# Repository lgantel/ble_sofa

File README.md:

# BLE Sofa
Control module for CIAR sofa using custom BLE interface.

## Overview

The sofa command box is powered over a 4 pins RJ9 connector. The voltage measured at the command box input is 29V. It is provided by the motor (LM35_05) which gets its power from the PS10 adapter (29V - 2A).

The command box has three cable inputs:
- The RJ9 connector for power supply and motor commands
- The left input (J1) connected to the sensitive button; It corresponds to the Down command.
- The right input (J3) connected to the other sensitive button; It corresponds to the Up command.

## Power Supply and Motor Commands

The RJ9 connector provides 4 wires connection which supplies power from the motor to the control box, and Up and Down commands from the control box to the motor.

## Issue with the current system

Currently the command box is connected to the Up and Down button with electrical wires. The issue comes when moving the sofa up and down, the cables are compressed by the mechanical part and end up being damaged.

## Replacement Solution

A replacement solution has been specified to allow the user to control the sofa using a wireless BLE application. The system would be based on a Raspberry Pi Pico W module which permits to easily control the motor through two electrical relays, and to receive commands from the user via the Bluetooth stack.

# Tools Setup

## Get the SDK and examples

```bash
cd pico
git clone https://github.com/raspberrypi/pico-sdk.git --branch master
cd pico-sdk
git submodule update --init
cd ..
git clone https://github.com/raspberrypi/pico-examples.git --branch master
```

## Install the toolchain

1. Install dependencies:

```bash
sudo apt update
sudo apt install cmake gcc-arm-none-eabi libnewlib-arm-none-eabi build-essential libstdc++-arm-none-eabi-newlib pkg-config libusb-1.0-0-dev
```

2. In the bashrc file, export the path to the SDK:

```bash
#
# RPi Pico SDK
#
export PICO_SDK_PATH=/home/laurent/Projects/lgantel/ble_sofa/pico/pico-sdk
```

3. To complete the installation, install `picotool` which is used to generate the UF2 binaries for the Raspberry Pi Pico:

```bash
git clone https://github.com/raspberrypi/picotool.git
cd picotool
mkdir build && cd build
cmake ..
make
sudo make install
```

# Example Projects

```bash
cd pico/workspace
mkdir build
cd build
```

The following examples can be built:

- [LED Control](doc/example_projects.md#led-control)
- [BLE Control](doc/example_projects.md#ble-control)
- [FreeRTOS App](doc/example_projects.md#freertos-app)
- [Relay Control](doc/example_projects.md#relay-control)

# Firmware loading via OpenOCD

1. Install OpenOCD:

```bash
sudo apt-get install pkg-config libjim-dev
git clone https://github.com/raspberrypi/openocd.git
cd openocd
git submodule update --init --recursive
./bootstrap
./configure --enable-picoprobe --enable-sysfsgpio --enable-bcm2835gpio
make -j8
sudo make install
```

2. Connect a USB cable to the Rasperry Pi Pico

3. Program Flash and verify:

```bash
./openocd_launch.sh
```

# BLE Sofa Application

- [BLE Sofa Application Documentation](doc/ble_sofa_app.md#ble_sofa_app)

# Resources

## Raspberry Pi Pico

* Raspberry Pi Pico power pins information:

https://dronebotworkshop.com/pi-pico/

* A nice development kit PCB example for Raspberry Pi Pico:

https://01001000.xyz/2021-02-13-Raspberry-Pi-Pico-dev-board-Kiwikit/

* C library for LCD OLED:

https://github.com/martinkooij/pi-pico-ss-oled

* Information on the debug probes:

https://www.framboise314.fr/tout-nouveau-la-sonde-de-debogage-raspberry-pi-debug-probe/

* Kicad symbol and footprint models:

https://github.com/bdubs-astro/Raspberry_Pi_Pico_W_Kicad_Files

## Bluetooth Low Energy

* Bluetooth BLE resources:

http://tvaira.free.fr/bts-sn/activites/activite-ble/bluetooth-ble.html#gatt-et-att

https://novelbits.io/bluetooth-gatt-services-characteristics/

https://www.jaredwolff.com/get-started-with-bluetooth-low-energy/

https://punchthrough.com/android-ble-guide/

https://mcuoneclipse.com/2023/03/19/ble-with-wifi-and-freertos-on-raspberry-pi-pico-w/

## Pico W Web Server

* https://github.com/krzmaz/pico-w-webserver-example
* https://github.com/carlk3/FreeRTOS-FAT-CLI-for-RPi-Pico/tree/master/examples/wifi_httpd
* https://www.hackster.io/rajivcodelab/how-to-build-a-rest-api-on-raspberry-pi-pico-w-control-led-91b25b

- Rest API client:

https://stackoverflow.com/questions/72252577/what-is-the-simplest-way-to-make-a-post-request-in-kotlin-for-android-app

```bash
curl -X POST "http://192.168.1.31:80/api/control-led" -d '{"led": 0}' -H 'Content-Type: application/json'
```

## Flash Storage

* Tutorial on how to modify linker script to reserve a flash memory block for persistent storage:

https://community.element14.com/products/raspberry-pi/b/blog/posts/raspberry-pico-c-sdk-reserve-a-flash-memory-block-for-persistent-storage

* Example code for Flash read/write:

https://github.com/raspberrypi/pico-examples/blob/master/flash/program/flash_program.c

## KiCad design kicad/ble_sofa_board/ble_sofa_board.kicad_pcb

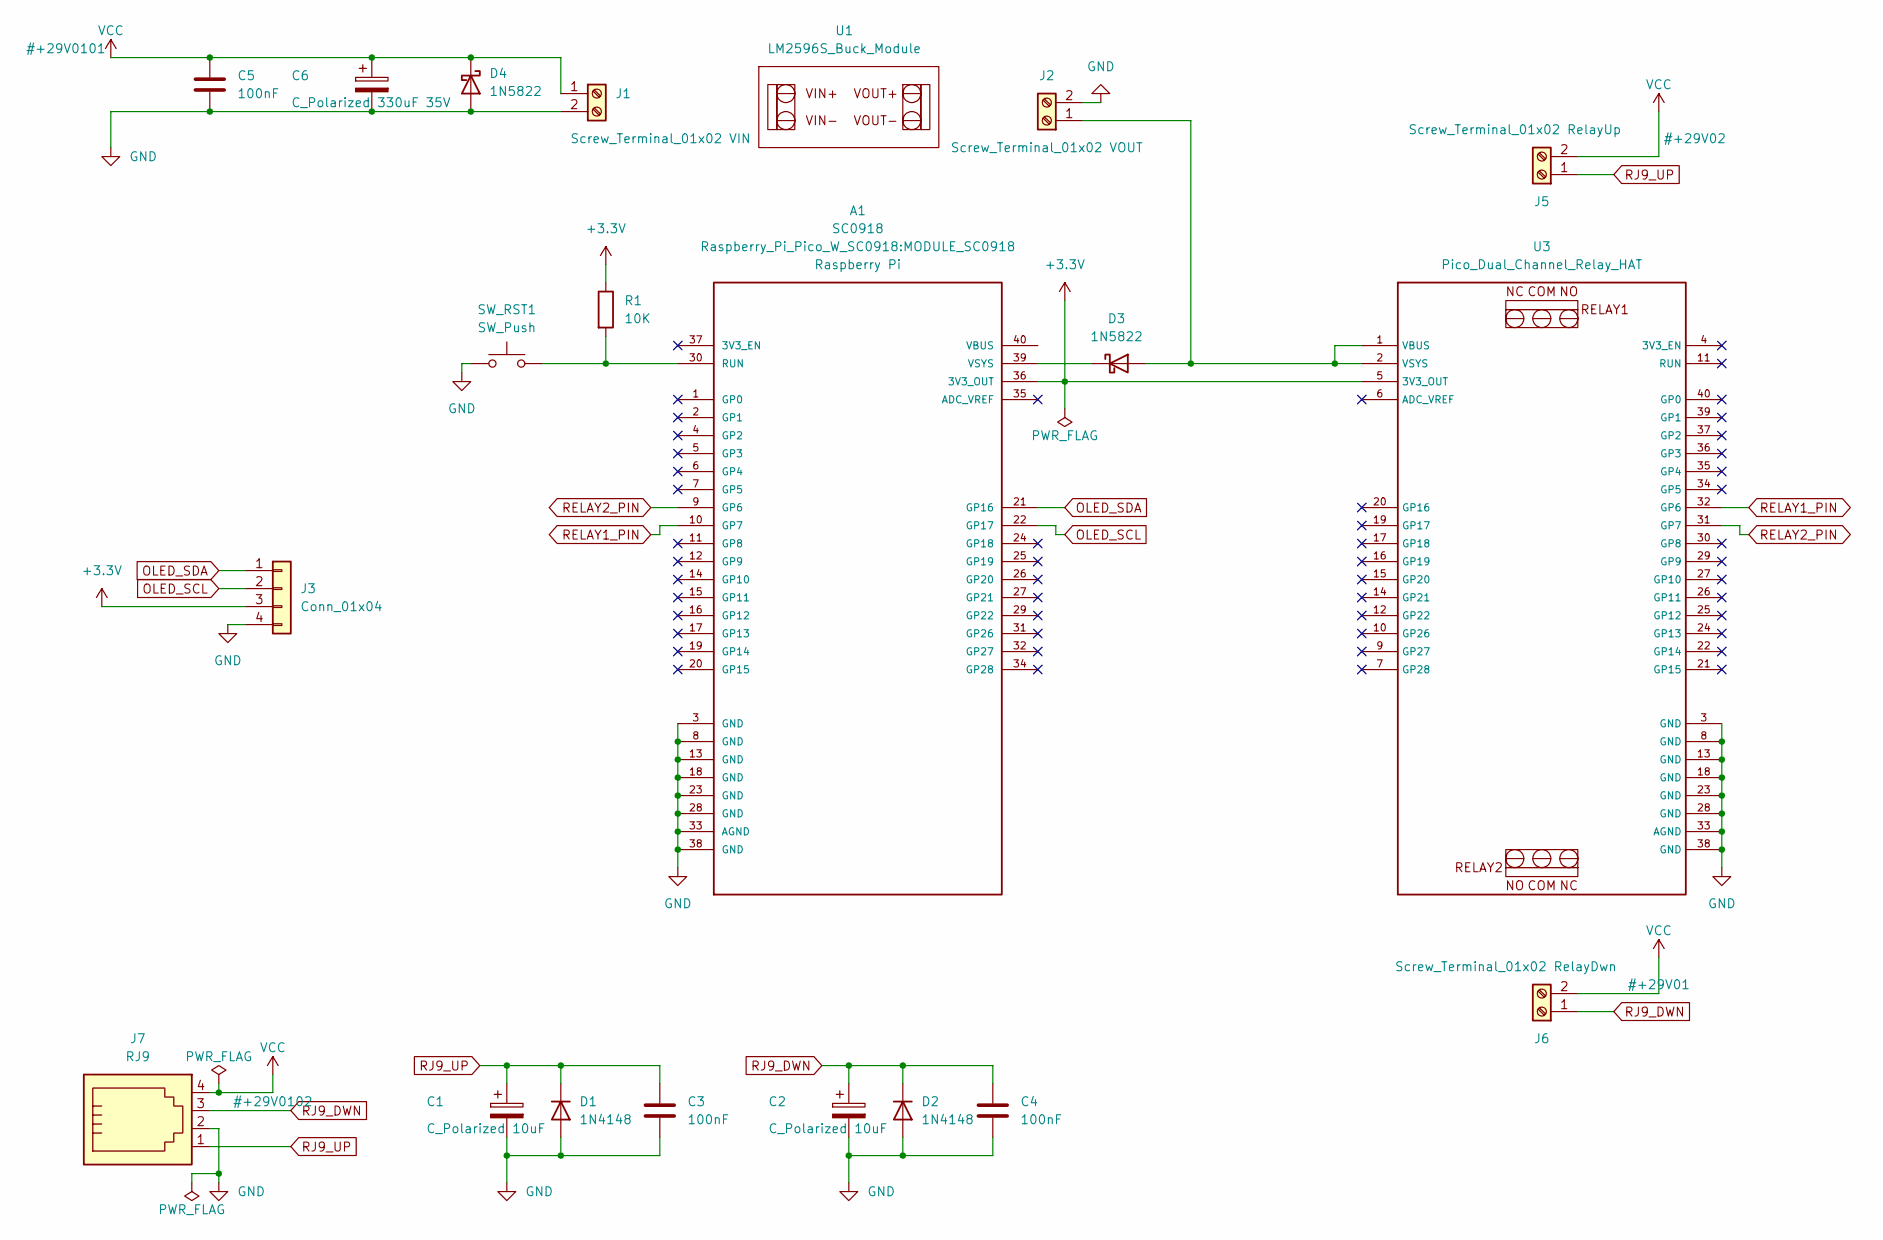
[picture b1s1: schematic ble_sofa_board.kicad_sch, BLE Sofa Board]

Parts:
A1: SC0918; MODULE_SC0918; PARTREV 1.6
C1, C2: C_Polarized 10uF; CP_Radial_D5.0mm_P2.00mm
C3, C4, C5: 100nF; C_Disc_D7.0mm_W2.5mm_P5.00mm
C6: C_Polarized 330uF 35V; CP_Radial_D10.0mm_P5.00mm
D1, D2: 1N4148; D_DO-35_SOD27_P7.62mm_Horizontal
D3, D4: 1N5822; D_DO-201AD_P15.24mm_Horizontal
J1: Screw_Terminal_01x02 VIN; TerminalBlock_bornier-2_P5.08mm
J2: Screw_Terminal_01x02 VOUT; TerminalBlock_bornier-2_P5.08mm
J3: Conn_01x04; OLED_I2C_128x32_SSD1306
J5: Screw_Terminal_01x02 RelayUp; TerminalBlock_bornier-2_P5.08mm
J6: Screw_Terminal_01x02 RelayDwn; TerminalBlock_bornier-2_P5.08mm
J7: RJ9; 4P4C_narrow
R1: 10K; R_Axial_DIN0207_L6.3mm_D2.5mm_P10.16mm_Horizontal
SW_RST1: SW_Push; SW_PUSH_6mm_H4.3mm
U1: LM2596S_Buck_Module
U3: Pico_Dual_Channel_Relay_HAT

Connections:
+3.3V: A1.36 (3V3_OUT), J3.3, R1.1, U3.5 (3V3_OUT)
GND: A1.3 (GND), A1.8 (GND), A1.13 (GND), A1.18 (GND), A1.23 (GND), A1.28 (GND), A1.33 (AGND), A1.38 (GND), C1.2, C2.2, C3.2, C4.2, C5.2, C6.2, D1.2 (A), D2.2 (A), D4.2 (A), J1.2, J2.2, J3.4, J7.2, SW_RST1.1, U3.3 (GND), U3.8 (GND), U3.13 (GND), U3.18 (GND), U3.23 (GND), U3.28 (GND), U3.33 (AGND), U3.38 (GND)
unnamed: A1.30 (RUN), R1.2, SW_RST1.2
unnamed: A1.39 (VSYS), D3.1 (K)
unnamed: D3.2 (A), J2.1, U3.1 (VBUS), U3.2 (VSYS)
OLED_SCL: A1.22 (GP17), J3.2
OLED_SDA: A1.21 (GP16), J3.1
RELAY1_PIN: A1.10 (GP7), U3.32 (GP6)
RELAY2_PIN: A1.9 (GP6), U3.31 (GP7)
RJ9_DWN: C2.1, C4.1, D2.1 (K), J6.1, J7.3
RJ9_UP: C1.1, C3.1, D1.1 (K), J5.1, J7.1
VCC: C5.1, C6.1, D4.1 (K), J1.1, J5.2, J6.2, J7.4

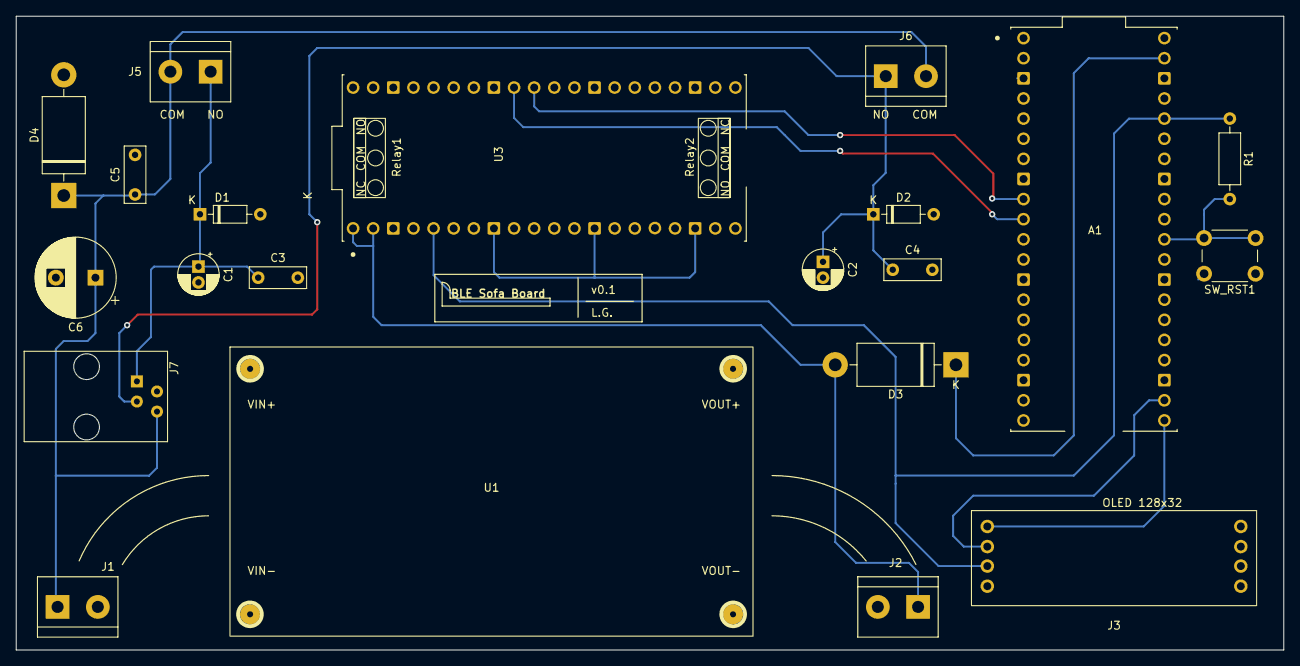
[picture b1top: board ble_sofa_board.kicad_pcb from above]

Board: 2 copper layers, 160.0 x 80.0 mm, 21 parts (0 on the bottom side), 12 nets.

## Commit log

2023-05-10 README - Add references
2023-06-02 README - Add information about original command box
2023-06-03 tests - Add project to test LED control
2023-06-04 README - Add instructions for tools setup
2023-06-06 README - Add instructions to compile examples
2023-06-06 ble_control - Add WIP project
2023-06-12 ble_control - WIP main program
2023-06-19 ble_control - Complete and validate app.
2023-06-19 read_ina219 - Add test application
2023-06-28 ble_control - Cleanup and adapt app. to remotely control a LED
2023-07-09 relay_control - Add project to test relays before BLE interfacing
2023-07-10 README - Add schema for LED Control example
2023-07-10 README - Complete BLE Control project doc.
2023-07-15 ble_control - WIP Android app for BLE test
2023-07-28 ble_control - Complete Android app for BLE test
2023-07-29 ble_control - Add Android project XML files
2023-08-26 ble_control - Update comments
2023-09-07 relay_control - Validate project and complete doc
2023-09-29 ble_sofa_app - Add RPi Pico W firmware project
2023-09-29 ble_sofa_app - Add Android application
2023-10-20 ble_sofa_app - WIP specs diagram
2023-10-21 ble_sofa_app - Complete specs diagram
2023-10-22 ble_sofa_app - WIP - Add Kicad schematics and footprints
2023-10-22 ble_sofa_app - Add Raspberry Pi Pico W symbol, footprint and 3D model
2023-11-01 ble_sofa_board - WIP schematic
2023-11-12 ble_sofa_board - Complete schematic and PCB
2023-11-20 ble_sofa_board - Update gnd in diagram
2023-12-06 ble_sofa_board - diagram - update PNG image and capacitors values
2023-12-24 ble_sofa_diagram - Update
2023-12-28 ble_sofa_diagram - Add 3v3 RUN pullup + buck input capacitor
2023-12-28 oled_control - WIP SSD1306
2023-12-29 oled_control - Init. and pixel display OK
2023-12-29 oled_control - Add support to display strings
2023-12-30 ble_sofa_app - Update schematic
2023-12-30 ble_sofa_app - Fix ERC in schematic
2023-12-31 ble_sofa_app - WIP integrate OLED lib.
2024-01-01 ble_sofa_app - ssd1306: refactor lib.
2024-01-13 pico-workspace - Make lib for SSD1306
2024-01-13 pico-workspace - Make lib for relay control
2024-01-14 ble_sofa_app - Integrate SSD1306 OLED display
2024-02-03 ble_sofa - diagram - Add soft start circuit and OLED display
2024-02-03 ble_sofa - pcb - Update to Kicad 7
2024-02-10 ble_sofa - pcb - Update schematics with soft start circuit and OLED display
2024-02-11 ble_sofa - Update PCB layout
2024-02-12 ble_sofa - pcb - Add LM2596S buck module 3D model
2024-02-24 ble_sofa - pcb - Add RJ9 4P4C connector 3D model
2024-03-06 ble_sofa - pcb - WIP Pico dual channel relay hat 3D model
2024-03-16 ble_sofa - pcb - Add Pico dual channel relay hat 3D model
2024-03-16 ble_sofa - pcb - WIP routing
2024-03-17 ble_sofa - pcb - Complete routing
2024-03-17 ble_sofa - pcb - Minor update + Gerber files generation
2024-03-23 ble_sofa - pcb - Update Gerber files
2024-09-13 ble_sofa - Box - Add WIP FreeCAD design
2024-09-18 ble_sofa - Box - WIP FreeCAD design
2024-09-21 ble_sofa - Box - Complete design
2024-09-28 ble_sofa - Lid - Setup shape and dimensions
2024-10-01 Kicad - Add TODO file for v0.2
2024-10-03 ble_sofa - Lid - Add holes for displays, leds and buttons
2024-10-07 ble_sofa - Lid - Reduce width and add hole for relays
2024-10-27 examples - Add FreeRTOS example application
2024-10-27 examples - Remove FreeRTOS sources from repository
2024-10-27 examples - Add FreeRTOS sources as a submodule
2024-10-27 pico - Cleanup repo
2024-11-17 examples - Add WiFi scanning application
2024-12-23 examples - Complete WiFi app with networks sorting and connection/disconnection
2025-09-11 ble_sofa - Lid, Box - Fix. holes and pads
2025-09-11 ble_sofa - Update README with OpenOCD installation instructions
2025-10-21 ble_sofa - Lid - Add glass holders
2025-10-21 3d printer - Add test design for bed leveling
2025-12-06 ble_sofa_app - Upgrade Android Studio app
2025-12-14 ble_sofa_app - Add linker script to create custom persistent storage area
2025-12-14 tools - Make openocd_launch script more generic
2025-12-16 ble_sofa_app - Add FreeRTOS tasks + access from C to persistent Flash section
2026-01-24 ble_sofa_app - Add completed Android app
2026-01-24 ble_sofa_app - WIP C app
2026-01-24 ble_sofa_app - Add completed Python app
